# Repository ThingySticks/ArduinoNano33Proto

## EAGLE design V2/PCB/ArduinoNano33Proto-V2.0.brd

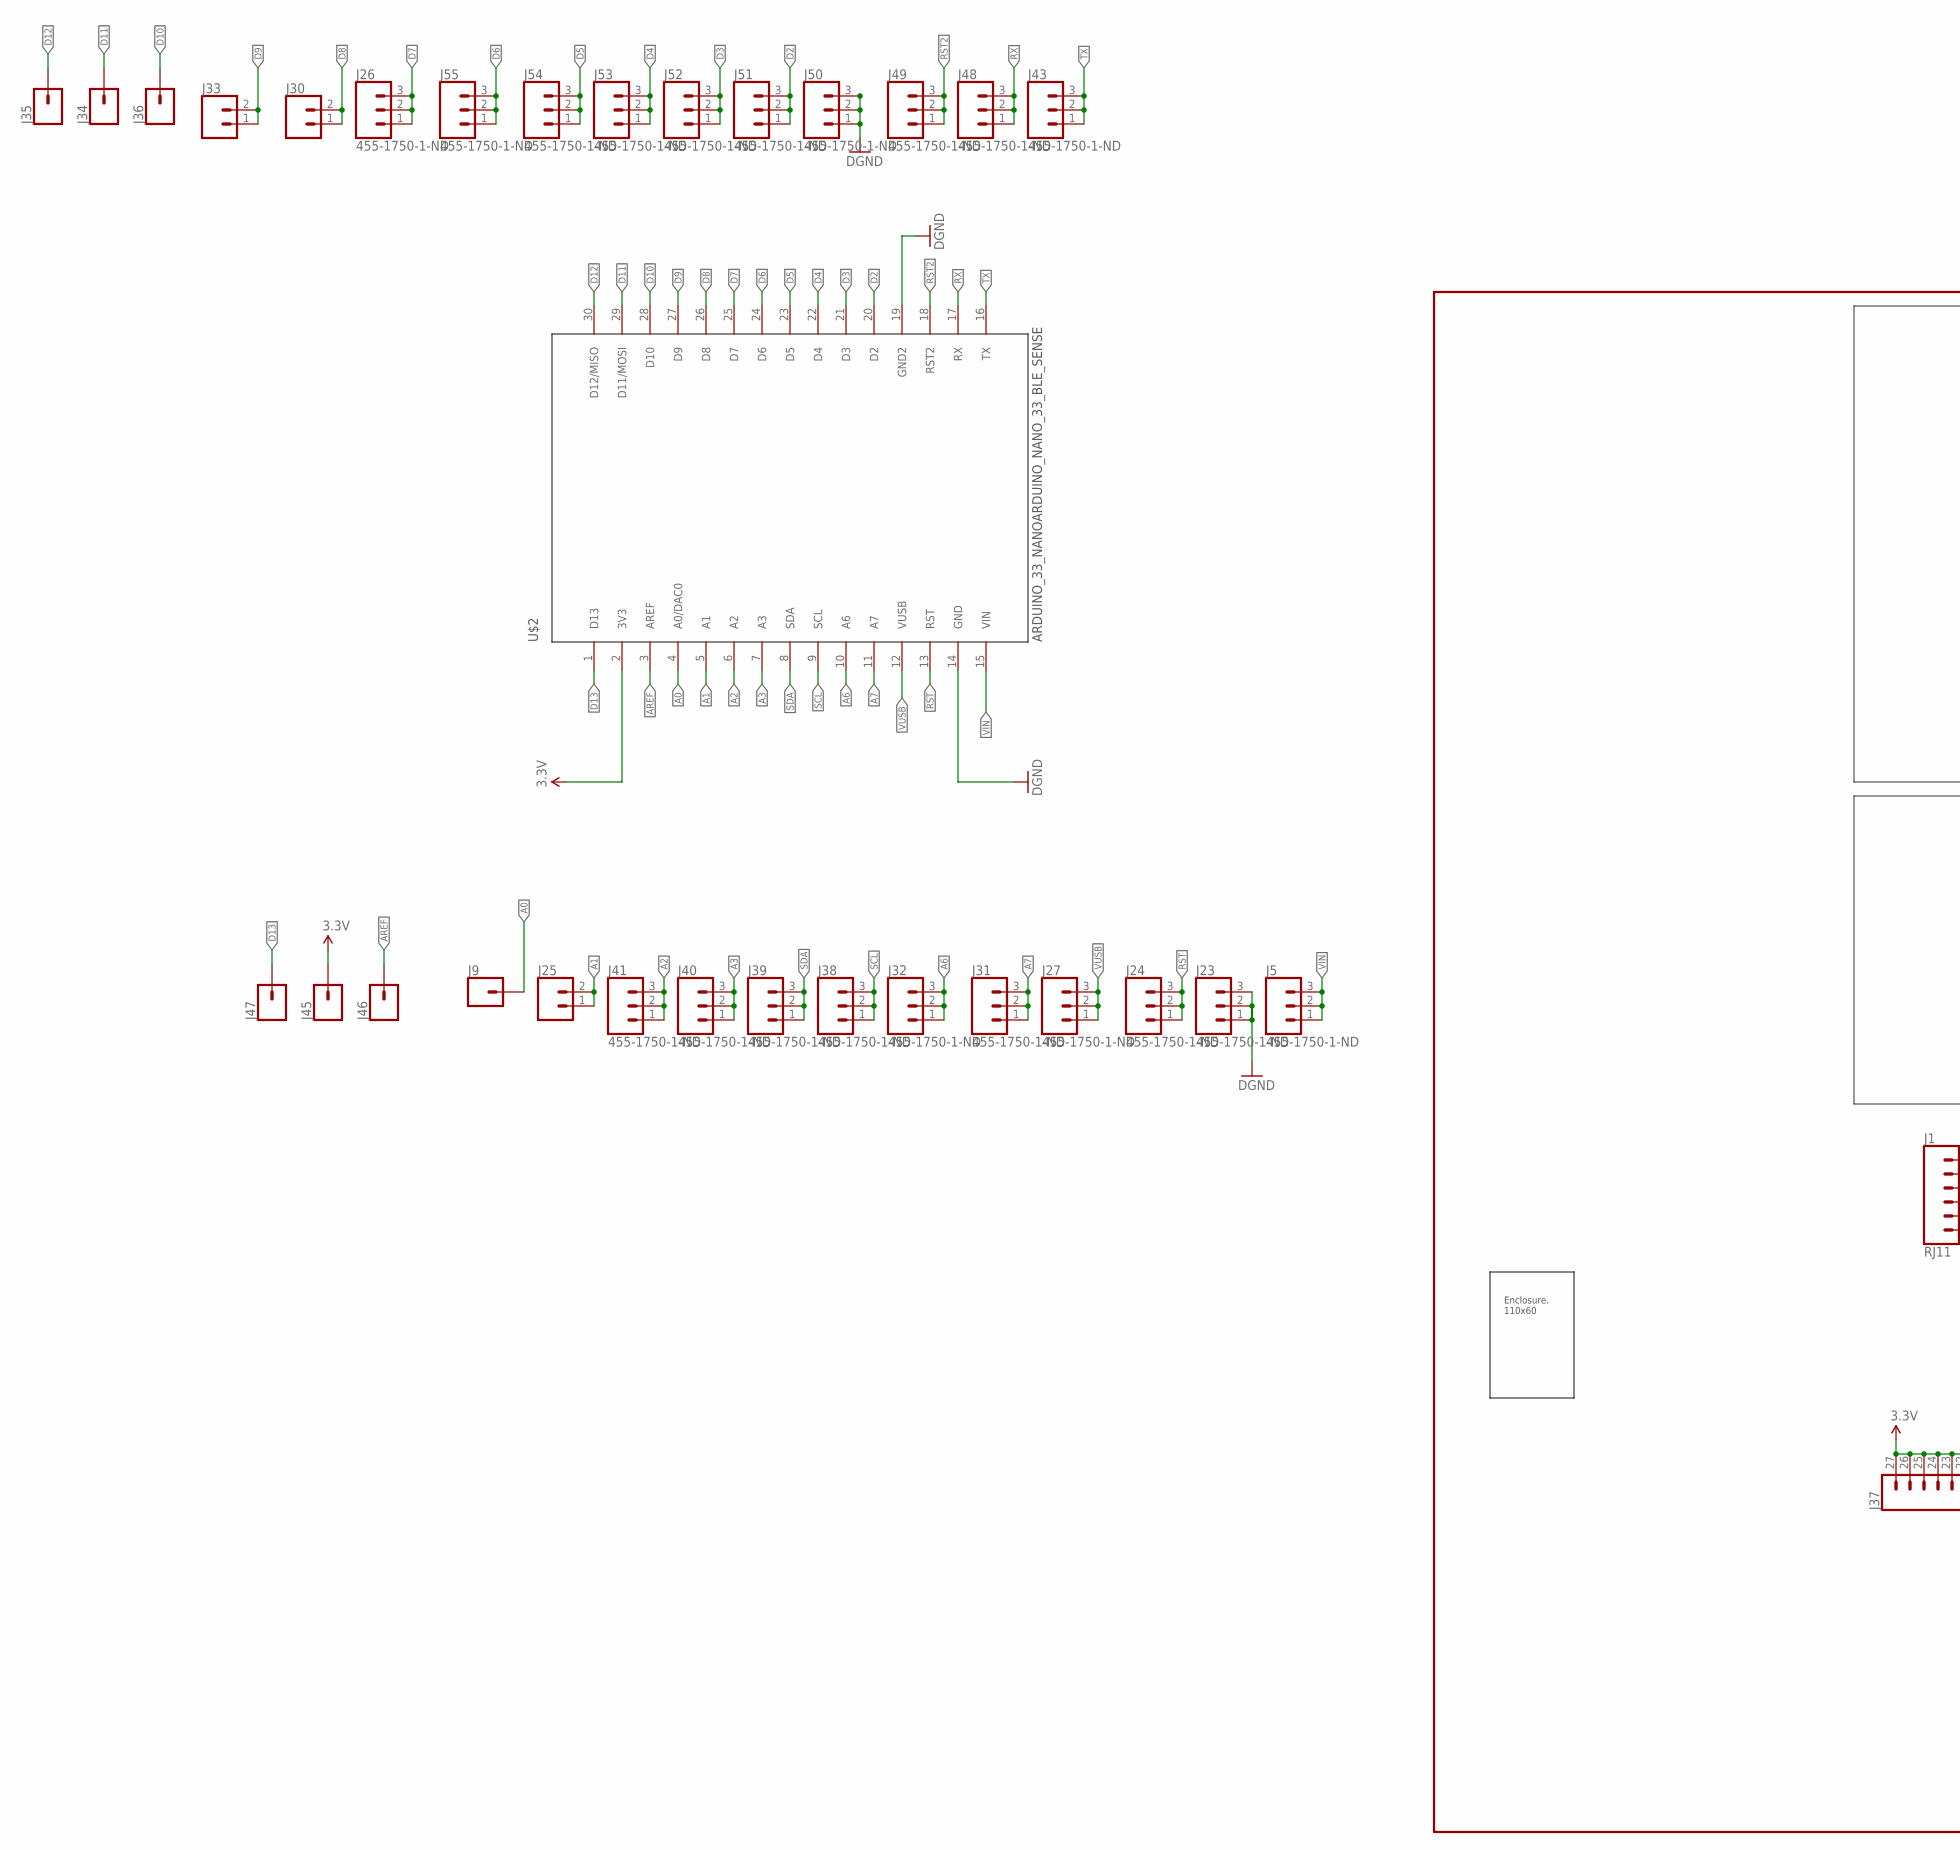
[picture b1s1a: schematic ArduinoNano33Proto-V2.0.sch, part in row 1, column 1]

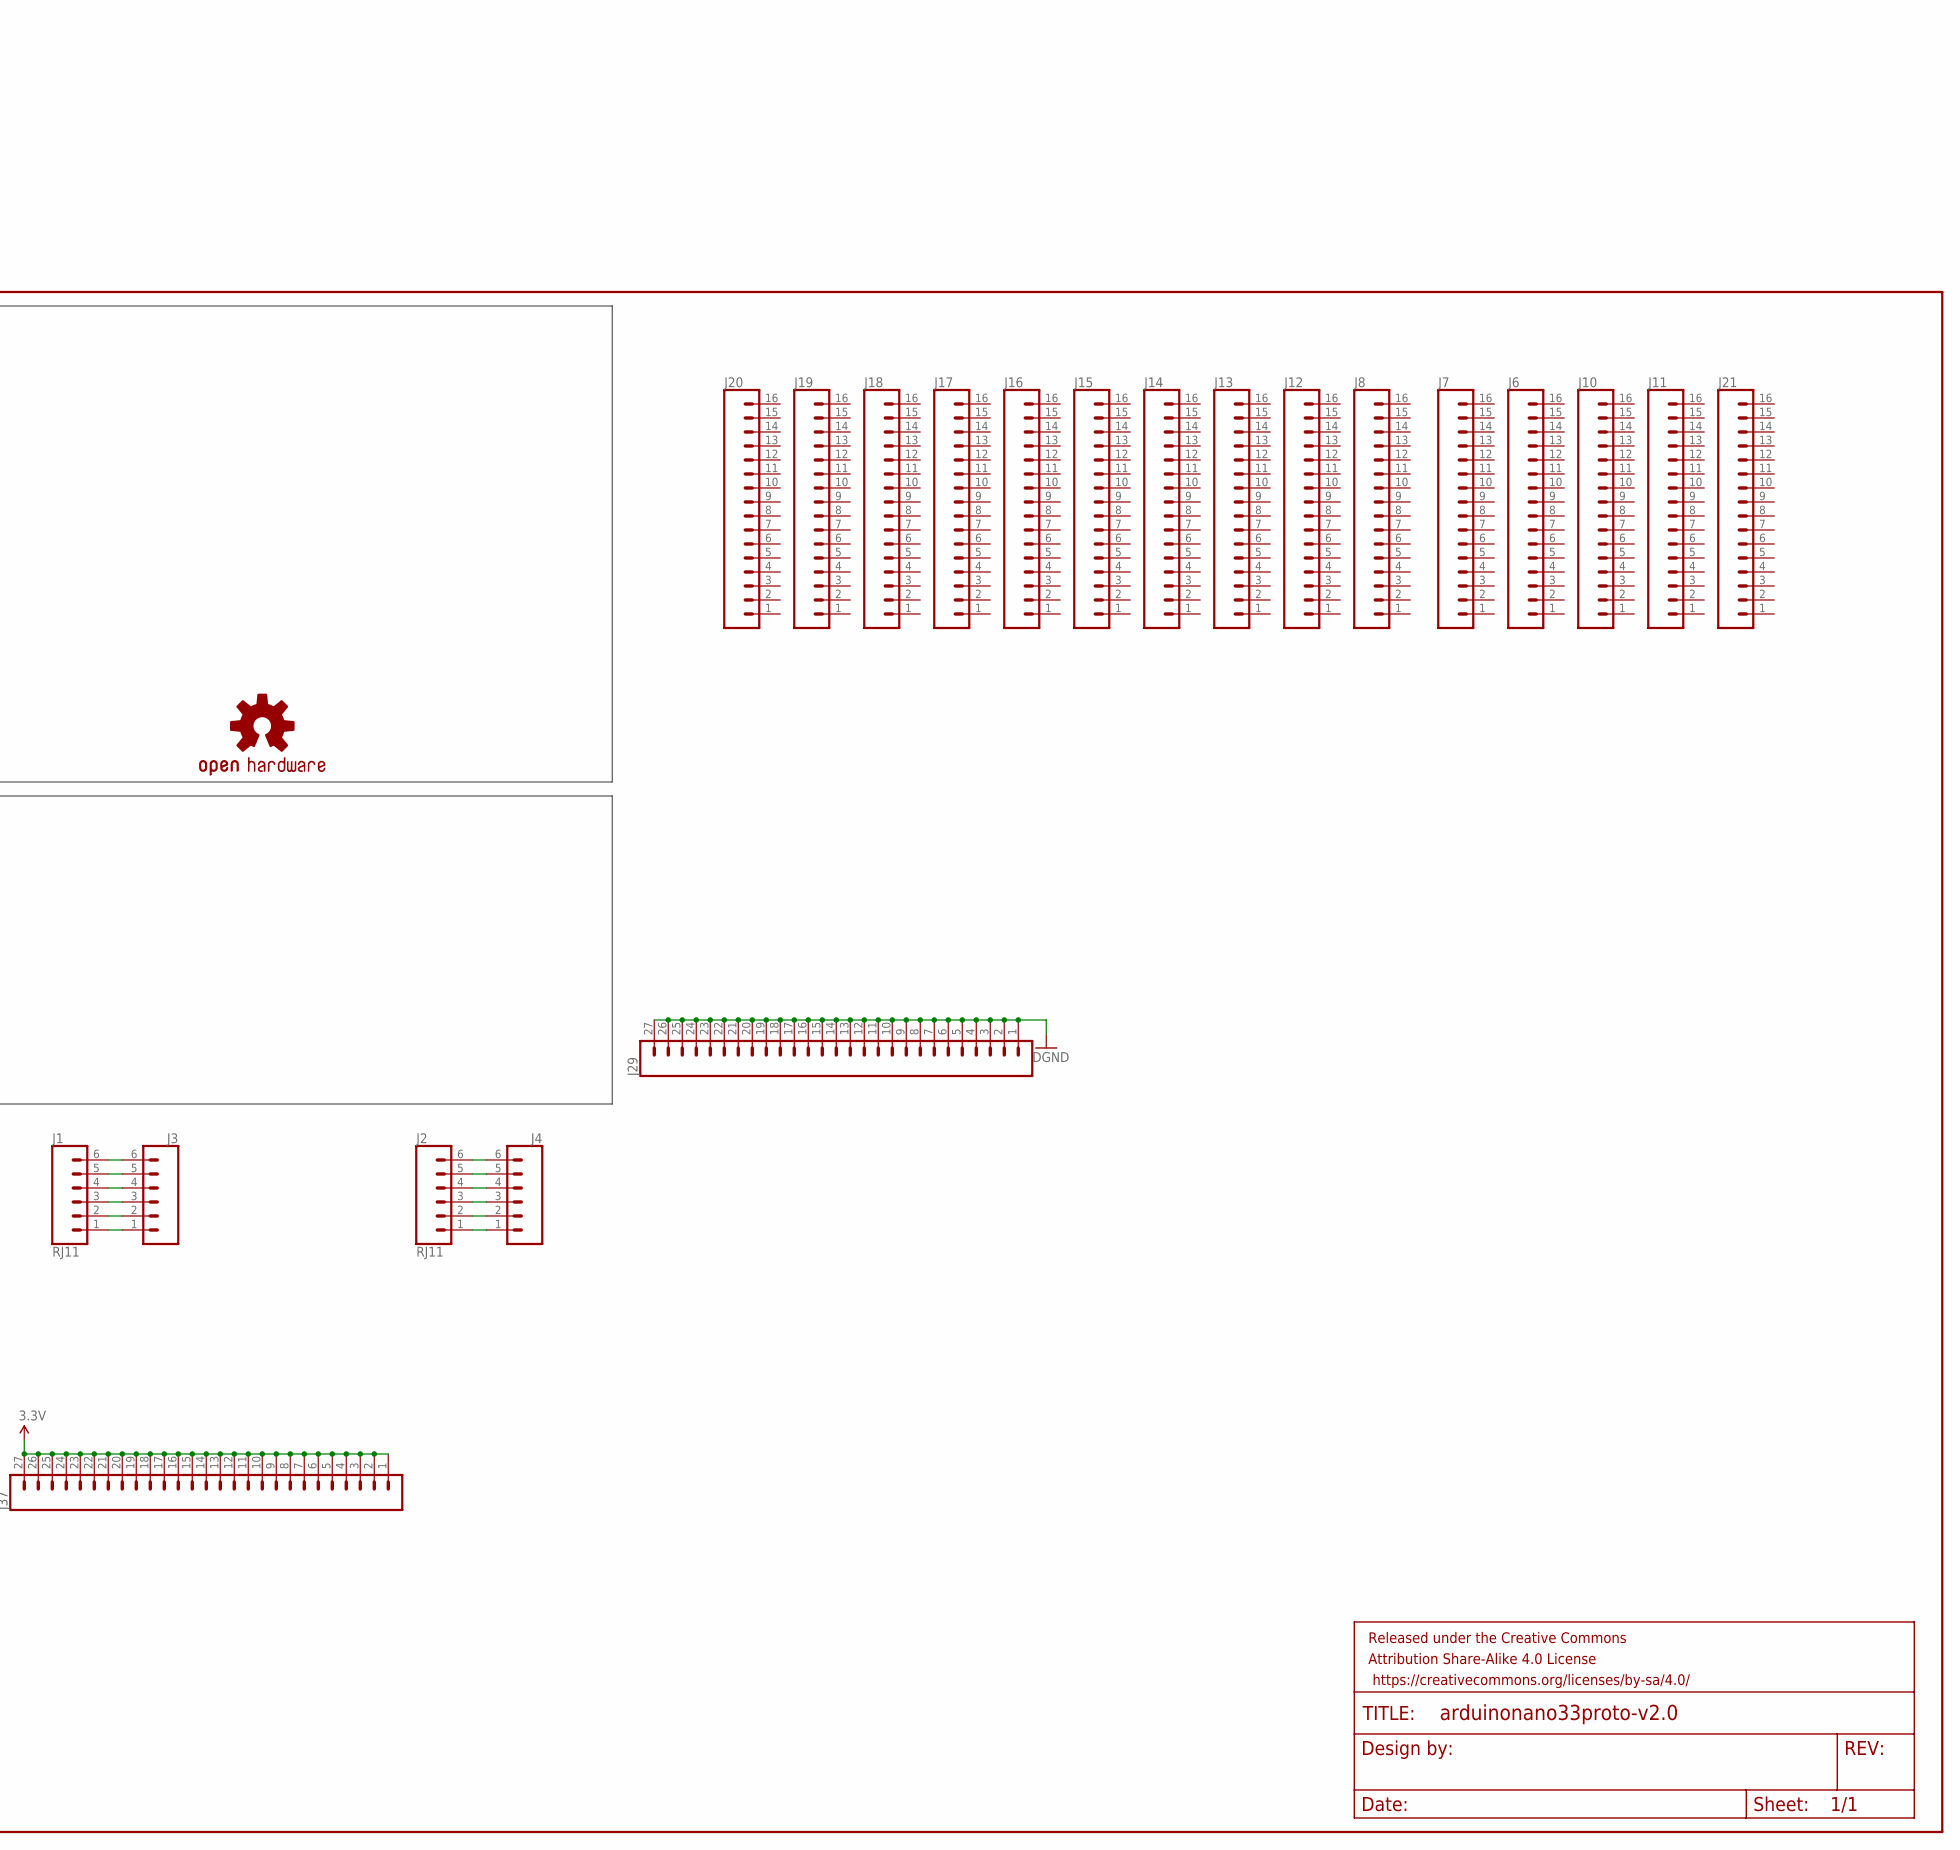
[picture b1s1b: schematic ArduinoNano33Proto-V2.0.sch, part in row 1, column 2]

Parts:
FRAME2: FRAME-LEDGER; CREATIVE_COMMONS
J1, J2: RJ11; RJ11-6
J3, J4: CONN_06SILK_FEMALE_PTH; 1X06
J5, J23, J24, J26, J27, J31, J32, J38, J39, J40, J41, J43, J48, J49, J50, J51, J52, J53, J54, J55: 455-1750-1-ND; 1X03
J6, J7, J8, J10, J11, J12, J13, J14, J15, J16, J17, J18, J19, J20, J21: CONN_161X16_NO_SILK; 1X16_NO_SILK
J9, J34, J35, J36, J45, J46, J47: CONN_01PTH_NO_SILK_YES_STOP; 1X01_NO_SILK
J25, J30, J33: CONN_02; 1X02
J29, J37: CONN_27; 1X27
LOGO1: OSHW-LOGOM; OSHW-LOGO-M
U$1: CAMDENBOSS-ENCLOSURE-110X60BOTH-EXTENDED-WIDE; CAMDENBOSS_ENCLOSURE_110X60_WIDE_EXTENDED
U$2: ARDUINO_33_NANOARDUINO_NANO_33_BLE_SENSE; ARDUINO_NANO_33

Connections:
3.3V: J37.1, J37.2, J37.3, J37.4, J37.5, J37.6, J37.7, J37.8, J37.9, J37.10, J37.11, J37.12, J37.13, J37.14, J37.15, J37.16, J37.17, J37.18, J37.19, J37.20, J37.21, J37.22, J37.23, J37.24, J37.25, J37.26, J37.27, J45.1, U$2.2 (3V3)
A0: J9.1, U$2.4 (A0/DAC0)
A1: J25.1, J25.2, U$2.5 (A1)
A2: J41.1, J41.2, J41.3, U$2.6 (A2)
A3: J40.1, J40.2, J40.3, U$2.7 (A3)
A6: J32.1, J32.2, J32.3, U$2.10 (A6)
A7: J31.1, J31.2, J31.3, U$2.11 (A7)
AREF: J46.1, U$2.3 (AREF)
D2: J51.1, J51.2, J51.3, U$2.20 (D2)
D3: J52.1, J52.2, J52.3, U$2.21 (D3)
D4: J53.1, J53.2, J53.3, U$2.22 (D4)
D5: J54.1, J54.2, J54.3, U$2.23 (D5)
D6: J55.1, J55.2, J55.3, U$2.24 (D6)
D7: J26.1, J26.2, J26.3, U$2.25 (D7)
D8: J30.1, J30.2, U$2.26 (D8)
D9: J33.1, J33.2, U$2.27 (D9)
D10: J36.1, U$2.28 (D10)
D11: J34.1, U$2.29 (D11/MOSI)
D12: J35.1, U$2.30 (D12/MISO)
D13: J47.1, U$2.1 (D13)
GND: J23.1, J23.2, J23.3, J29.1, J29.2, J29.3, J29.4, J29.5, J29.6, J29.7, J29.8, J29.9, J29.10, J29.11, J29.12, J29.13, J29.14, J29.15, J29.16, J29.17, J29.18, J29.19, J29.20, J29.21, J29.22, J29.23, J29.24, J29.25, J29.26, J29.27, J50.1, J50.2, J50.3, U$2.14 (GND), U$2.19 (GND2)
unnamed: J1.6, J3.6
unnamed: J1.5, J3.5
unnamed: J1.4, J3.4
unnamed: J1.3, J3.3
unnamed: J1.2, J3.2
unnamed: J1.1, J3.1
unnamed: J2.1, J4.1
unnamed: J2.2, J4.2
unnamed: J2.3, J4.3
unnamed: J2.4, J4.4
unnamed: J2.5, J4.5
unnamed: J2.6, J4.6
RST: J24.1, J24.2, J24.3, U$2.13 (RST)
RST2: J49.1, J49.2, J49.3, U$2.18 (RST2)
RX: J48.1, J48.2, J48.3, U$2.17 (RX)
SCL: J38.1, J38.2, J38.3, U$2.9 (SCL)
SDA: J39.1, J39.2, J39.3, U$2.8 (SDA)
TX: J43.1, J43.2, J43.3, U$2.16 (TX)
VIN: J5.1, J5.2, J5.3, U$2.15 (VIN)
VUSB: J27.1, J27.2, J27.3, U$2.12 (VUSB)

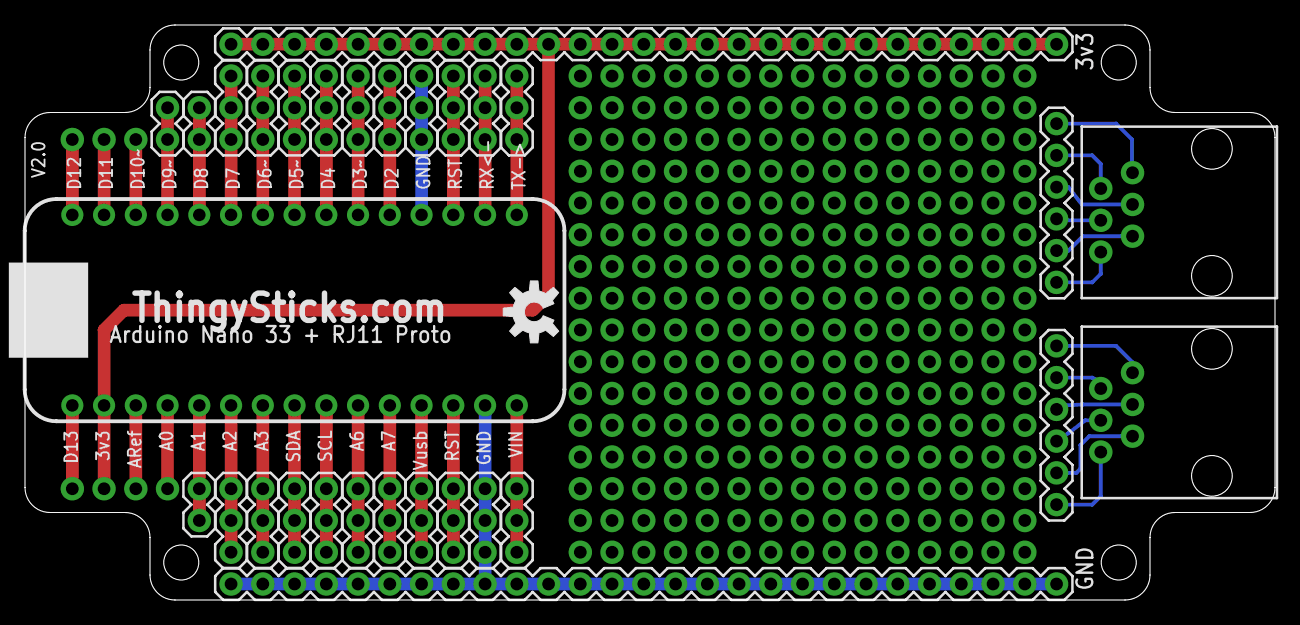
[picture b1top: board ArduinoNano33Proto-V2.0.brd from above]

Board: 2 copper layers, 100.0 x 46.0 mm, 55 parts (0 on the bottom side), 41 nets.

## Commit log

2019-08-17 First pass at RJ11 Protoboard.
2020-03-30 Adding V3 (basic version)
2020-03-30 Update to V2 (RJ11) board.

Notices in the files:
parts and their libraries:
SparkFun-Aesthetics: Licensing: Creative Commons ShareAlike 4.0 International - https://creativecommons.org/licenses/by-sa/4.0
SparkFun-Aesthetics: Released under the Creative Commons Attribution Share-Alike 4.0 License
SparkFun-Aesthetics: https://creativecommons.org/licenses/by-sa/4.0
